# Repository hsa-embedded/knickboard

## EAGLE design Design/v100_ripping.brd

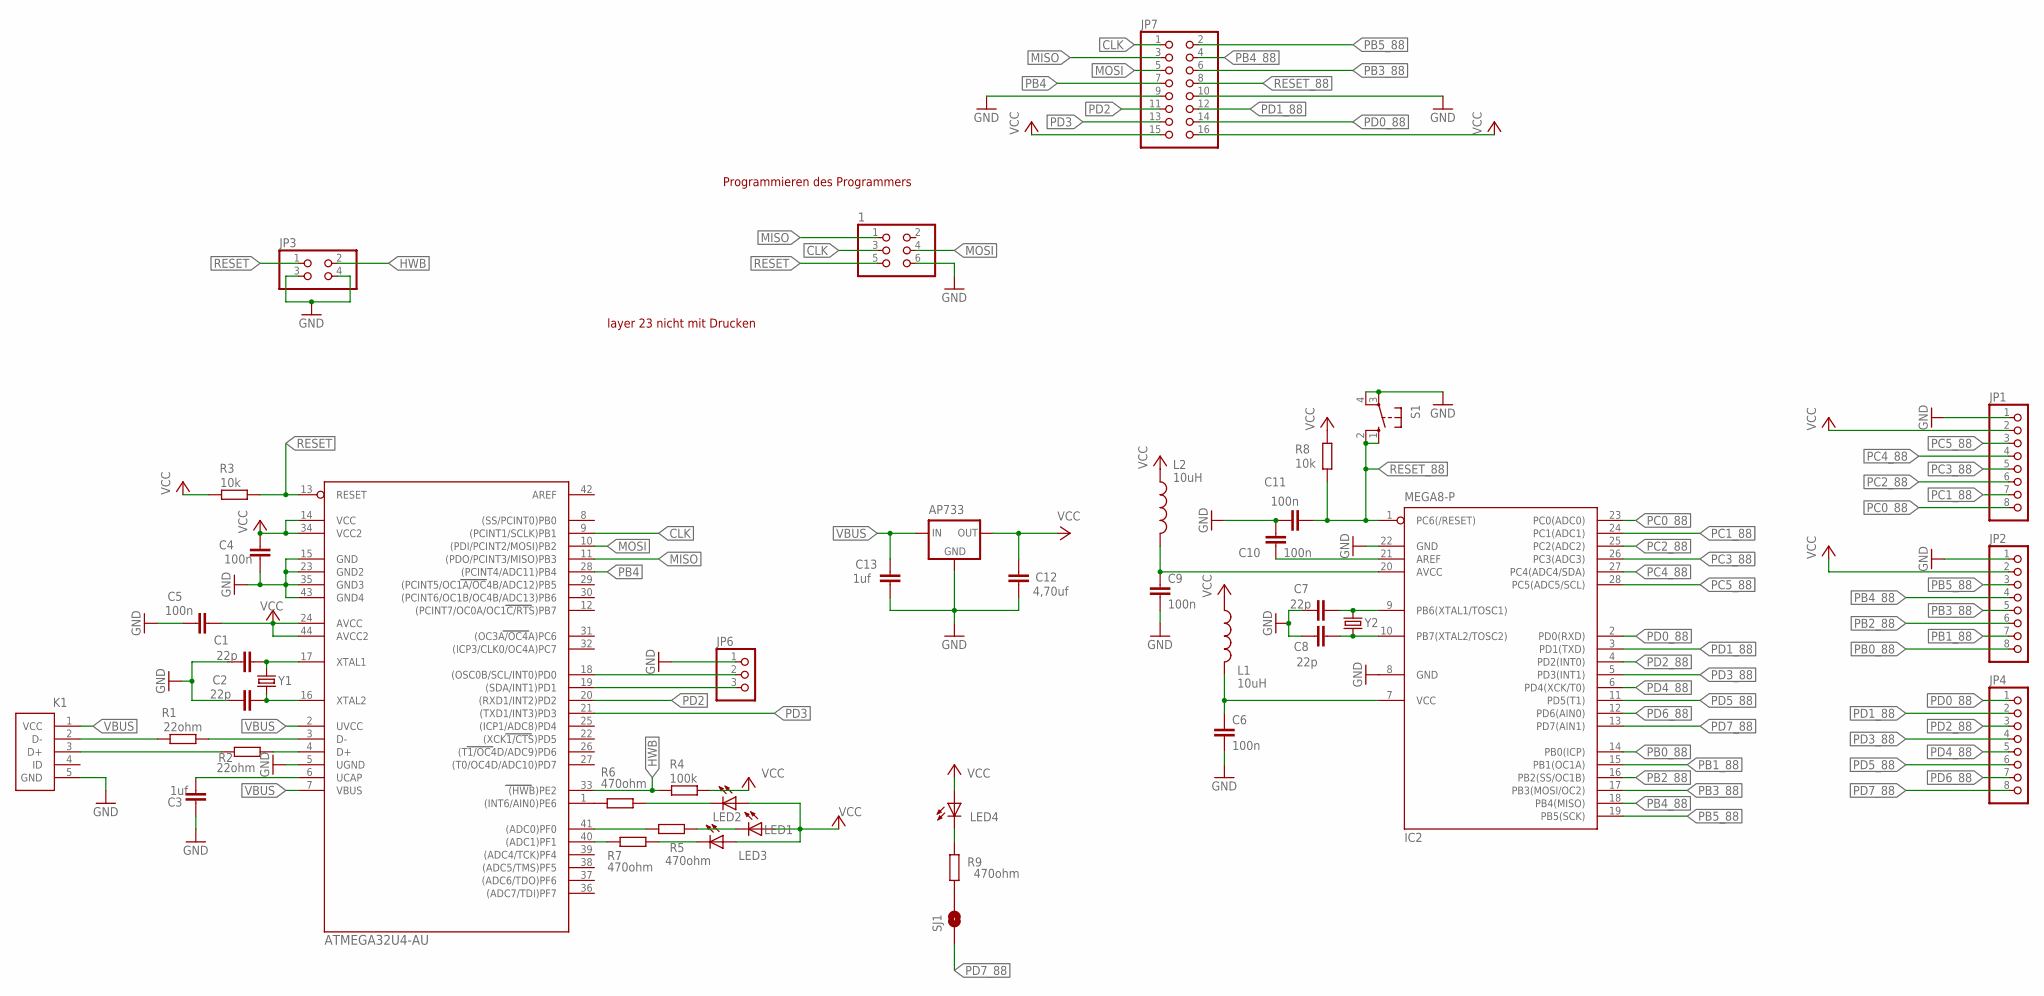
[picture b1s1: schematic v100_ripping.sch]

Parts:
1: PINHD-2X3; 2X03
C1, C2, C7, C8: 22p; C0805
C3, C13: 1uf; C0805
C4, C5: 100n; C0805
C6, C9, C10, C11: 100n; 0805
C12: 4,70uf; C0805
IC1: ATMEGA32U4-AU; TQFP44
IC2: MEGA8-P; DIL28-3
JP1, JP2, JP4: PINHD-1X8; 1X08
JP3: PINHD-2X2; 2X02
JP6: PINHD-1X3; 1X03
JP7: PINHD-2X8; 2X08
K1: 65100516121
L1, L2: 10uH; 0805
LED1, LED2, LED3, LED4: LED_LEDCHIP-LED0805; LED_CHIP-LED0805
R1, R2: 22ohm; R0805
R3, R8: 10k; R0805
R4: 100k; R0805
R5, R6, R7, R9: 470ohm; R0805
S1: SWITCH-OMRON_10-XX; SWITCH-OMRON_B3F-10XX
SJ1: SOLDERJUMPERTRACE; SJ_2S-TRACE
U$2: AP733
Y1, Y2: CRYSTALSMD; HC49UP

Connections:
CLK: 1.3, IC1.9 ((PCINT1/SCLK)PB1), JP7.1
D+: K1.3 (D+), R2.2
D-: K1.2 (D-), R1.2
GND: 1.6, C1.1, C2.1, C3.1, C4.1, C5.2, C6.2, C7.1, C8.1, C9.2, C10.1, C11.1, C12.2, C13.2, IC1.5 (UGND), IC1.15 (GND), IC1.23 (GND2), IC1.35 (GND3), IC1.43 (GND4), IC2.8 (GND), IC2.22 (GND), JP1.1, JP2.1, JP3.3, JP3.4, JP6.1, JP7.9, JP7.10, K1.5 (GND), S1.3, S1.4 (P1), U$2.3 (GND)
HWB: IC1.33 ((HWB)PE2), JP3.2, R4.2
MISO: 1.1, IC1.11 ((PDO/PCINT3/MISO)PB3), JP7.3
MOSI: 1.4, IC1.10 ((PDI/PCINT2/MOSI)PB2), JP7.5
unnamed: IC1.3 (D-), R1.1
unnamed: IC1.4 (D+), R2.1
unnamed: C2.2, IC1.16 (XTAL2), Y1.1
unnamed: C1.2, IC1.17 (XTAL1), Y1.2
unnamed: C3.2, IC1.6 (UCAP)
unnamed: C7.2, IC2.9 (PB6(XTAL1/TOSC1)), Y2.2
unnamed: IC1.1 ((INT6/AIN0)PE6), R6.2
unnamed: LED4.C, R9.1
unnamed: LED1.C, R5.1
unnamed: IC1.40 ((ADC1)PF1), R7.2
unnamed: R9.2, SJ1.2
unnamed: IC1.41 ((ADC0)PF0), R5.2
unnamed: C8.2, IC2.10 (PB7(XTAL2/TOSC2)), Y2.1
unnamed: C9.1, IC2.20 (AVCC), L2.2
unnamed: C6.1, IC2.7 (VCC), L1.2
unnamed: C10.2, IC2.21 (AREF)
unnamed: IC1.19 ((SDA/INT1)PD1), JP6.3
unnamed: LED2.C, R6.1
unnamed: IC1.18 ((OSC0B/SCL/INT0)PD0), JP6.2
unnamed: LED3.C, R7.1
PB0_88: IC2.14 (PB0(ICP)), JP2.8
PB1_88: IC2.15 (PB1(OC1A)), JP2.7
PB2_88: IC2.16 (PB2(SS/OC1B)), JP2.6
PB3_88: IC2.17 (PB3(MOSI/OC2)), JP2.5, JP7.6
PB4: IC1.28 ((PCINT4/ADC11)PB4), JP7.7
PB4_88: IC2.18 (PB4(MISO)), JP2.4, JP7.4
PB5_88: IC2.19 (PB5(SCK)), JP2.3, JP7.2
PC0_88: IC2.23 (PC0(ADC0)), JP1.8
PC1_88: IC2.24 (PC1(ADC1)), JP1.7
PC2_88: IC2.25 (PC2(ADC2)), JP1.6
PC3_88: IC2.26 (PC3(ADC3)), JP1.5
PC4_88: IC2.27 (PC4(ADC4/SDA)), JP1.4
PC5_88: IC2.28 (PC5(ADC5/SCL)), JP1.3
PD0_88: IC2.2 (PD0(RXD)), JP4.1, JP7.14
PD1_88: IC2.3 (PD1(TXD)), JP4.2, JP7.12
PD2: IC1.20 ((RXD1/INT2)PD2), JP7.11
PD2_88: IC2.4 (PD2(INT0)), JP4.3
PD3: IC1.21 ((TXD1/INT3)PD3), JP7.13
PD3_88: IC2.5 (PD3(INT1)), JP4.4
PD4_88: IC2.6 (PD4(XCK/T0)), JP4.5
PD5_88: IC2.11 (PD5(T1)), JP4.6
PD6_88: IC2.12 (PD6(AIN0)), JP4.7
PD7_88: IC2.13 (PD7(AIN1)), JP4.8, SJ1.1
RESET: 1.5, IC1.13 (RESET), JP3.1, R3.1
RESET_88: C11.2, IC2.1 (PC6(/RESET)), JP7.8, R8.1, S1.1 (S), S1.2 (S1)
VBUS: C13.1, IC1.2 (UVCC), IC1.7 (VBUS), K1.1 (VCC), U$2.1 (IN)
VCC: C4.2, C5.1, C12.1, IC1.14 (VCC), IC1.24 (AVCC), IC1.34 (VCC2), IC1.44 (AVCC2), JP1.2, JP2.2, JP7.15, JP7.16, L1.1, L2.1, LED1.A, LED2.A, LED3.A, LED4.A, R3.2, R4.1, R8.2, U$2.2 (OUT)

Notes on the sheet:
Programmieren des Programmers
layer 23 nicht mit Drucken

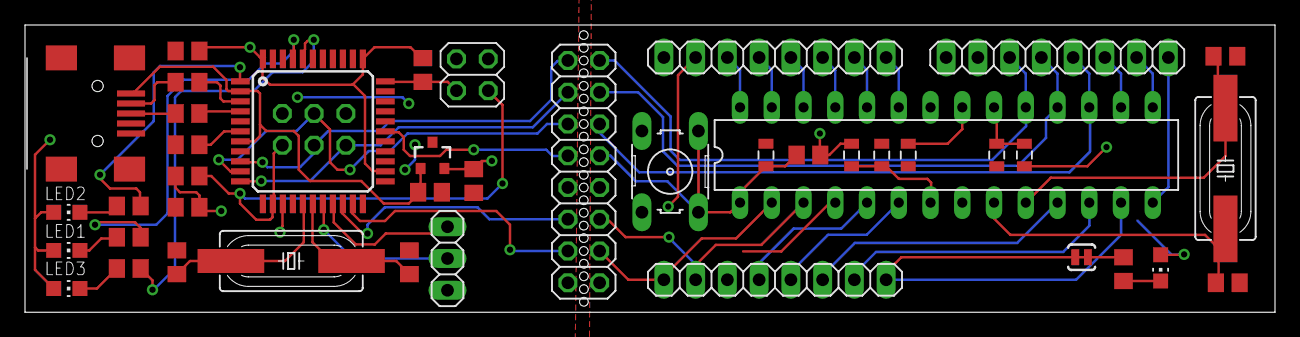
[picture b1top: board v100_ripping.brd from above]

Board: 2 copper layers, 100.0 x 23.0 mm, 43 parts (1 on the bottom side), 54 nets.

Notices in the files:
parts and their libraries:
SparkFun-FreqCtrl: Licensing: CC v3.0 Share-Alike You are welcome to use this library for commercial purposes.
